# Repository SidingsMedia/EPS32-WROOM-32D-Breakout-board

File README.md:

<!-- 
SPDX-FileCopyrightText: Copyright (c) 2021-2022 Sidings Media 

SPDX-License-Identifier: CC-BY-SA-4.0
-->
# ESP32-WROOM-32D Breakout boards
This project provides schematics for adaptor boards for the
ESP21-WROOM-32D. There are no components other that the WROOM module
included on the PCB.

## Licence
This repo uses the [REUSE](https://reuse.software) standard in order to
communicate the correct licence for the file. For those unfamiliar with
the standard the licence for each file can be found in one of three
places. The licence will either be in a comment block at the top of the
file, in a `.license` file with the same name as the file, or in the
dep5 file located in the `.reuse` directory. If you are unsure of the
licencing terms please contact
[contact@sidingsmedia.com](mailto:contact@sidingsmedia.com?subject=SMRC%20Licence).
All files committed to this repo must contain valid licencing
information or the pull request can not be accepted.

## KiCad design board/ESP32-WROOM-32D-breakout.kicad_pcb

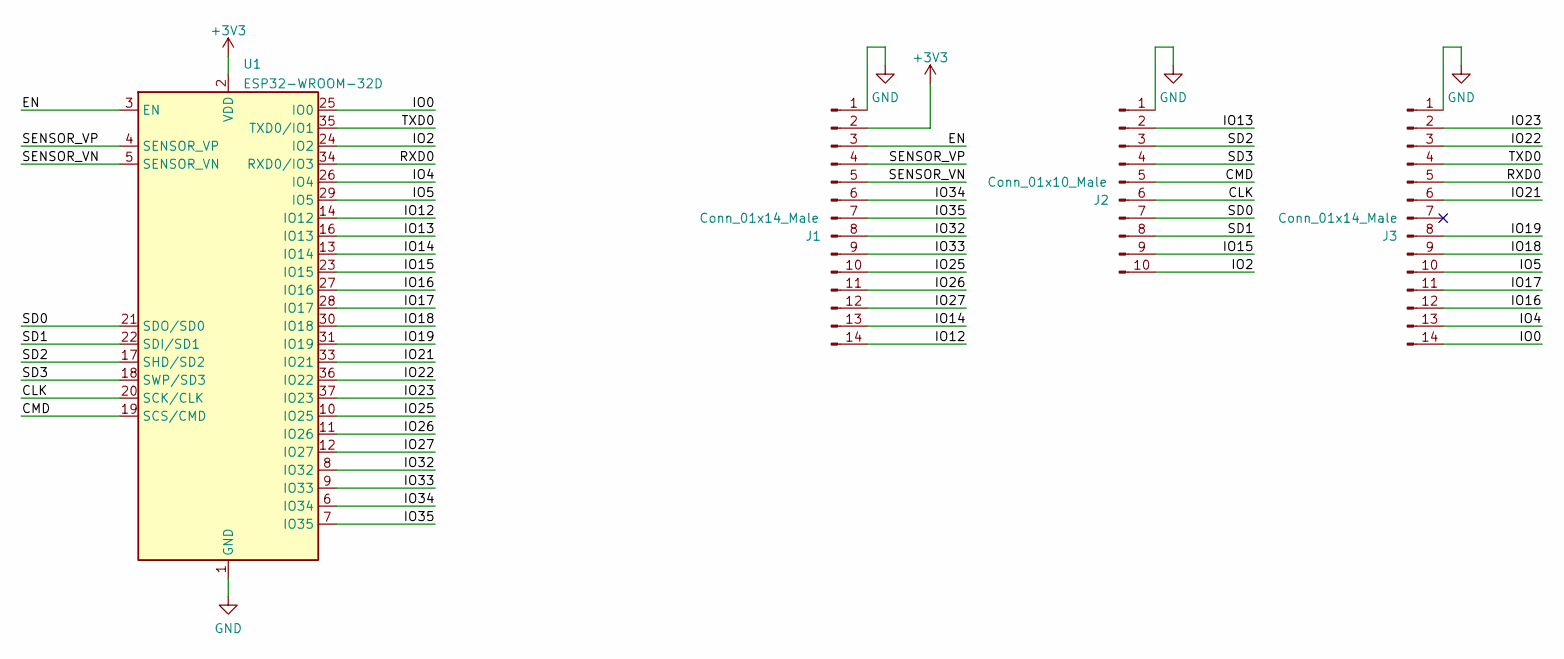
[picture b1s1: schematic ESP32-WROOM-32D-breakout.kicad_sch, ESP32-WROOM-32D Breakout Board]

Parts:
J1, J3: Conn_01x14_Male; PinHeader_1x14_P2.54mm_Vertical
J2: Conn_01x10_Male; PinHeader_1x10_P2.54mm_Vertical
U1: ESP32-WROOM-32D; ESP32-WROOM-32

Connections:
+3V3: J1.2, U1.2 (VDD)
/CLK: J2.6, U1.20 (SCK/CLK)
/CMD: J2.5, U1.19 (SCS/CMD)
/EN: J1.3, U1.3 (EN)
/IO0: J3.14, U1.25 (IO0)
/IO2: J2.10, U1.24 (IO2)
/IO4: J3.13, U1.26 (IO4)
/IO5: J3.10, U1.29 (IO5)
/IO12: J1.14, U1.14 (IO12)
/IO13: J2.2, U1.16 (IO13)
/IO14: J1.13, U1.13 (IO14)
/IO15: J2.9, U1.23 (IO15)
/IO16: J3.12, U1.27 (IO16)
/IO17: J3.11, U1.28 (IO17)
/IO18: J3.9, U1.30 (IO18)
/IO19: J3.8, U1.31 (IO19)
/IO21: J3.6, U1.33 (IO21)
/IO22: J3.3, U1.36 (IO22)
/IO23: J3.2, U1.37 (IO23)
/IO25: J1.10, U1.10 (IO25)
/IO26: J1.11, U1.11 (IO26)
/IO27: J1.12, U1.12 (IO27)
/IO32: J1.8, U1.8 (IO32)
/IO33: J1.9, U1.9 (IO33)
/IO34: J1.6, U1.6 (IO34)
/IO35: J1.7, U1.7 (IO35)
/RXD0: J3.5, U1.34 (RXD0/IO3)
/SD0: J2.7, U1.21 (SDO/SD0)
/SD1: J2.8, U1.22 (SDI/SD1)
/SD2: J2.3, U1.17 (SHD/SD2)
/SD3: J2.4, U1.18 (SWP/SD3)
/SENSOR_VN: J1.5, U1.5 (SENSOR_VN)
/SENSOR_VP: J1.4, U1.4 (SENSOR_VP)
/TXD0: J3.4, U1.35 (TXD0/IO1)
GND: J1.1, J2.1, J3.1, U1.1 (GND), U1.15 (GND), U1.38 (GND), U1.39 (GND)

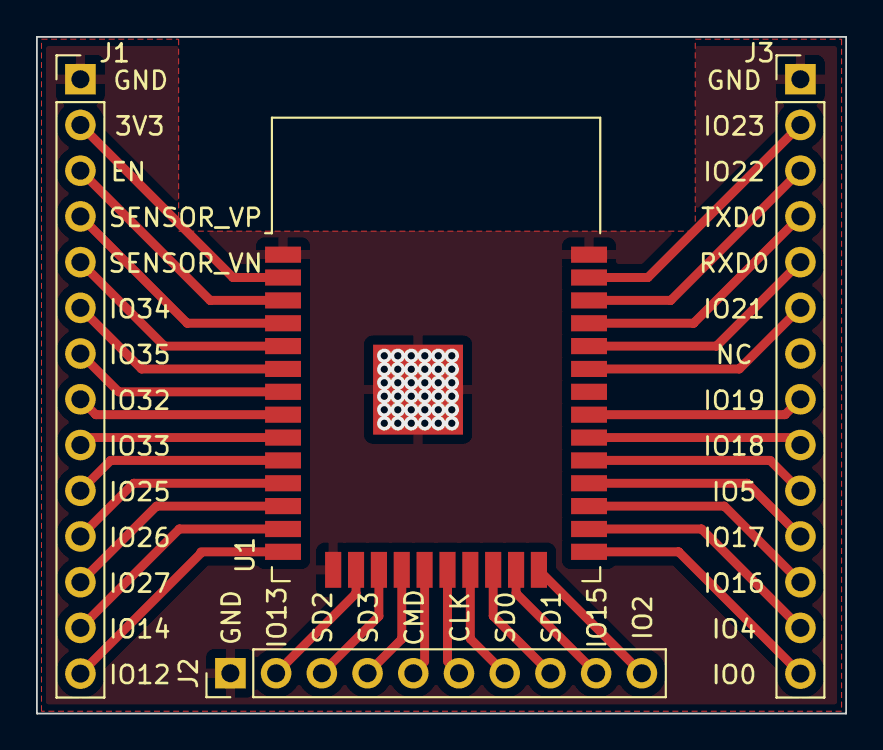
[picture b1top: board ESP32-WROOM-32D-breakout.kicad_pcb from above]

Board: 2 copper layers, 45.0 x 37.6 mm, 4 parts (0 on the bottom side), 35 nets.

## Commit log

2022-01-07 Repo configuration
2022-01-07 Fixed licence
2022-01-07 Finished basic design
2022-01-07 Fixed reuse
2022-01-07 Updated image
2022-01-07 Added image to readme
2022-01-08 Updated path to image

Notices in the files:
board/ESP32-WROOM-32D-breakout.kicad_pcb:
Licence: CC-BY-SA-4.0
